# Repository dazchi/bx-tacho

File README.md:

# BX Tacho

**English** | [繁體中文](README.zh-TW.md)

An open, DIY launch RPM meter for **Beyblade X** launchers. It clips onto the
back of the launcher, reads the launcher's spinning black/white pattern with an
IR sensor, and shows the launch RPM on a small OLED.

**Web app: [dazchi.github.io/bx-tacho](https://dazchi.github.io/bx-tacho/)**
(Chrome or Edge on a computer, Chrome on Android)

## What it does

- **Measures launch RPM** optically, up to about 20,000 RPM, and shows the
  result and the peak on the display.
- **Senses when a Bey is loaded** and when it's released, so each shot is
  recorded automatically: no buttons to press.
- **Keeps a shot history:** the last 50 shots, the total count, the best shot
  and the latest launch curve.
- **Bluetooth:** uses the Bey Battle Pass protocol, so Battle Pass apps can
  read your shots.
- **Runs on a 1S LiPo** with USB-C charging, a power switch, battery monitoring,
  and sleep when idle.
- **Left-handed mode:** the display can be turned 180°.

## Web app

The [web app](https://dazchi.github.io/bx-tacho/) runs in the browser, with
nothing to install:

- **Bluetooth:** live shot data, battery, the launch curve and your history.
- **Firmware updates** over USB or Bluetooth, with one click for the latest
  release.
- **A console** over USB or Bluetooth, for settings, calibration and
  diagnostics.

It's available in English, 繁體中文, 简体中文 and 日本語. Details:
[web/README.md](web/README.md).

## Hardware

An ESP32-C3 (ESP32-C3-WROOM-02) with two ITR8307 reflective IR sensors:
- one reads the RPM, through an LMV331 comparator;
- one detects a loaded Bey.

The rest of the board:
- a 0.96″ SSD1315 OLED;
- a TP4054 charger, with load sharing so it runs while charging;
- USB-C for power and data.

- [hardware/](hardware/): KiCad 10 project (schematic, PCB, footprints, 3D
  models). Gerbers and the BOM for JLCPCB assembly are in the
  [hardware v1.0 release](https://github.com/dazchi/bx-tacho/releases/tag/hw-v1.0).
- [mechanical/](mechanical/): STL files for the 3D-printed case:
  `case_top`, `case_bottom` and the launcher `clip`.

## Firmware

ESP-IDF v6.1 firmware in [firmware/](firmware/).

**Installing it:** use the web app's update button, or download the firmware
from [Releases](https://github.com/dazchi/bx-tacho/releases). Your settings
and shot history are kept.

**Building it yourself:**

```bash
cd firmware
idf.py build
idf.py -p COMx flash monitor
```

Build options, the console commands, calibration and the Bluetooth protocols
are covered in [firmware/README.md](firmware/README.md).

## License

[GPL-3.0-or-later](LICENSE). Copyright © 2026 Darren Chi
([github.com/dazchi](https://github.com/dazchi)). See [NOTICE](NOTICE) for
the exception covering the optional firmware extension.

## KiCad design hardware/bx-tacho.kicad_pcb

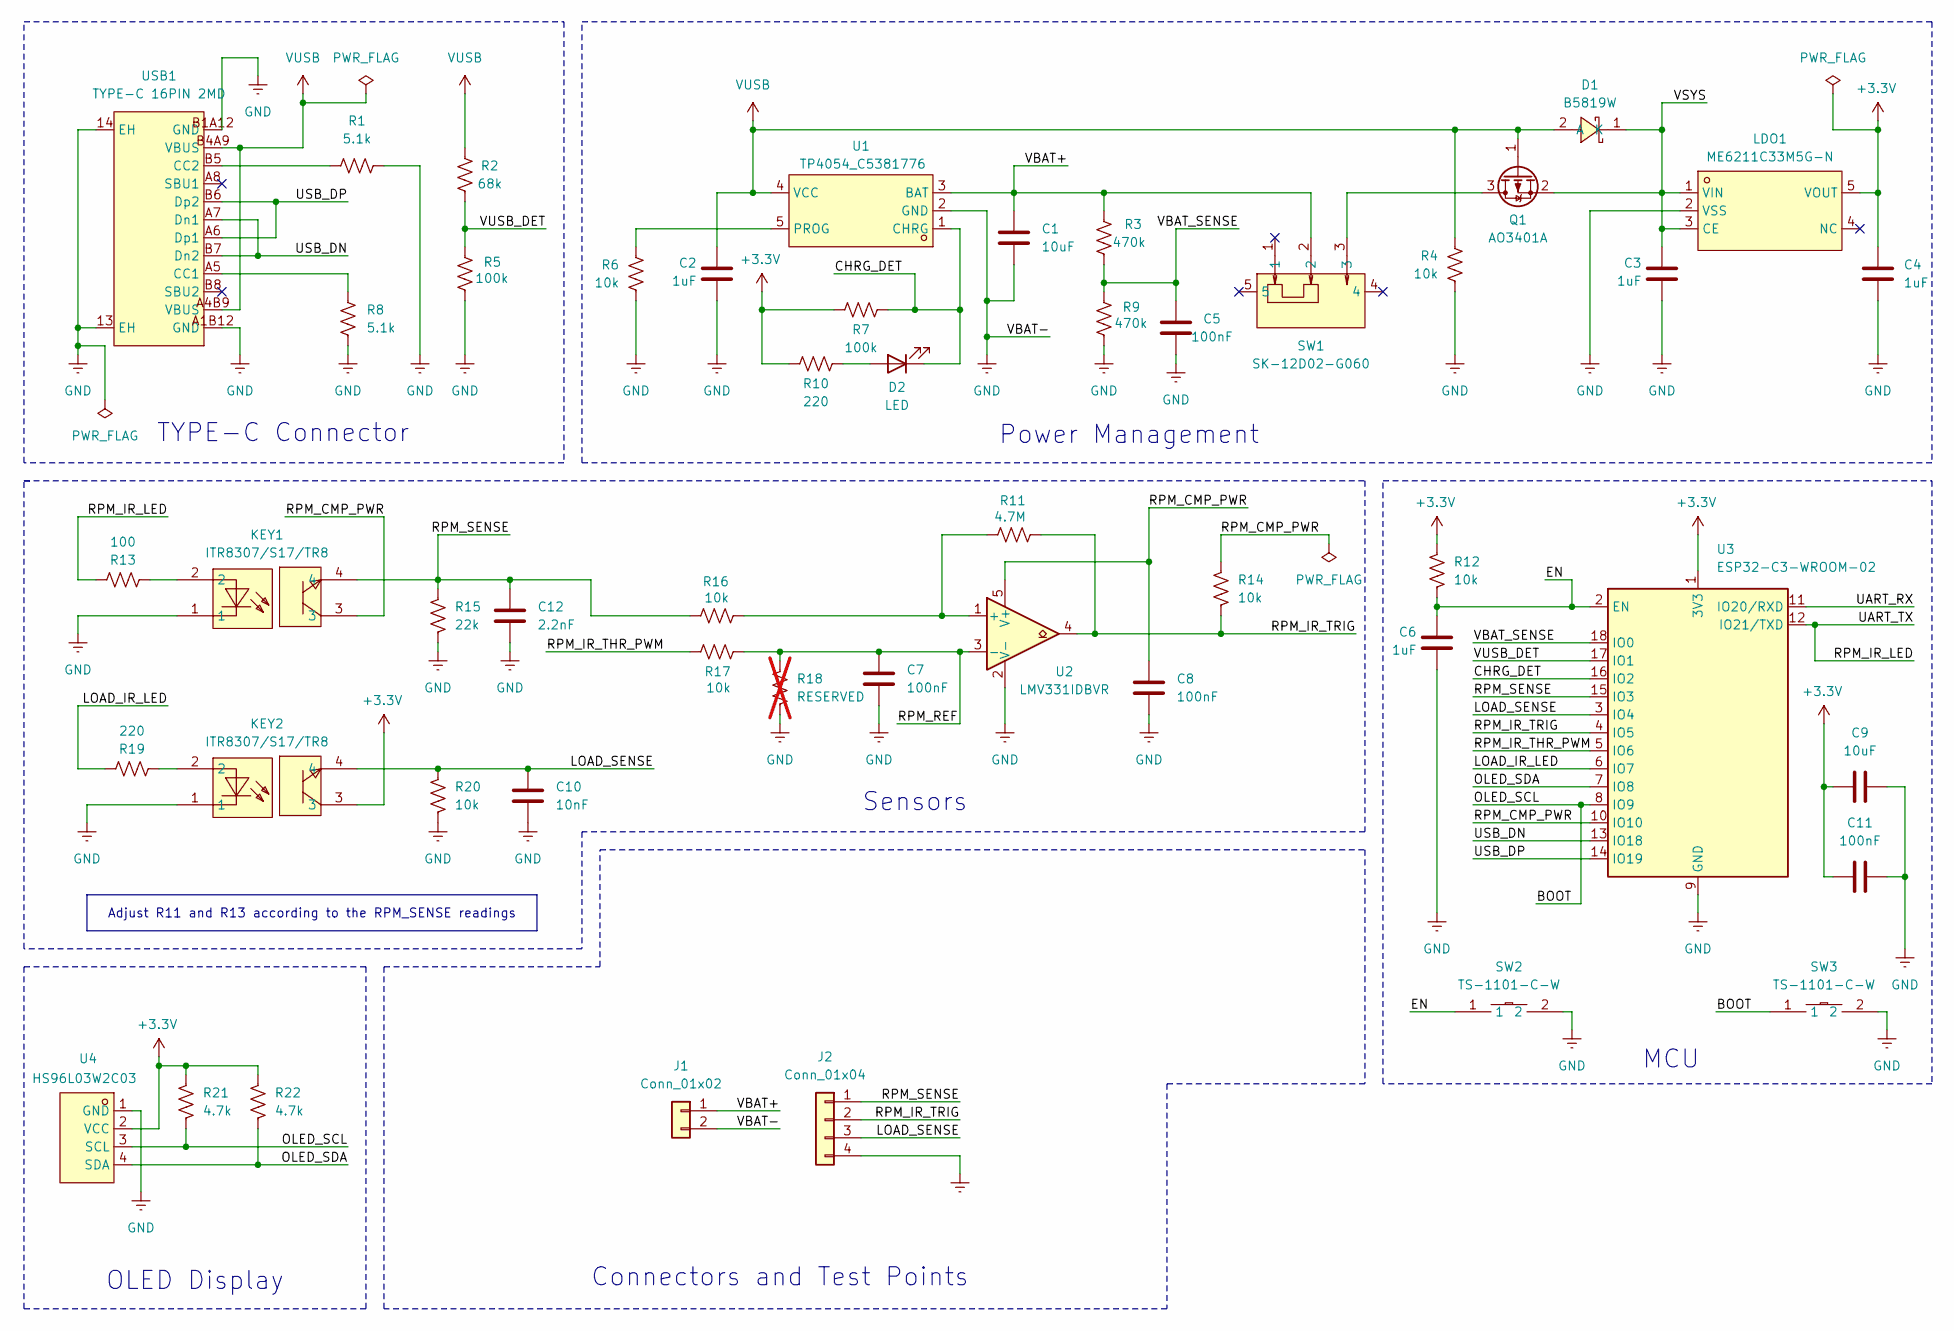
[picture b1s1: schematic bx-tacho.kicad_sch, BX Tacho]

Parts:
C1, C9: 10uF; C_0805_2012Metric; LCSC C15850
C2, C3, C4, C6: 1uF; C_0603_1608Metric; LCSC C15849
C5, C7, C8, C11: 100nF; C_0603_1608Metric; LCSC C14663
C10: 10nF; C_0603_1608Metric; LCSC C57112
C12: 2.2nF; C_0603_1608Metric; LCSC C1604
D1: B5819W; SOD-123F_L2.7-W1.6-LS3.8-RD-1; MPN B5819W SL; LCSC Part C8598
D2: LED; LED_0603_1608Metric_Pad1.05x0.95mm_HandSolder; LCSC C2286
J1: Conn_01x02; BatteryPads_1x02_SMD_2x3mm_P4mm
J2: Conn_01x04; PinHeader_1x04_P2.54mm_Vertical
KEY1, KEY2: ITR8307/S17/TR8; OPTO-SMD_ITR8307-S17-TR8-B-BL; MPN ITR8307/S17/TR8(B); LCSC Part C81632
LDO1: ME6211C33M5G-N; SOT-23-5_L3.0-W1.7-P0.95-LS2.8-BL; MPN ME6211C33M5G-N; LCSC Part C82942
Q1: AO3401A; SOT-23; LCSC C15127
R1, R8: 5.1k; R_0603_1608Metric; LCSC C23186
R2: 68k; R_0603_1608Metric; LCSC C23231
R3, R9: 470k; R_0603_1608Metric; LCSC C23178
R4, R6, R12, R14, R16, R17, R20: 10k; R_0603_1608Metric; LCSC C25804
R5, R7: 100k; R_0603_1608Metric; LCSC C25803
R10, R19: 220; R_0603_1608Metric; LCSC C22962
R11: 4.7M; R_0603_1608Metric; LCSC C2930153
R13: 100; R_0603_1608Metric; LCSC C22775
R15: 22k; R_0603_1608Metric; LCSC C31850
R18: RESERVED; R_0603_1608Metric; not fitted
R21, R22: 4.7k; R_0603_1608Metric; LCSC C23162
SW1: SK-12D02-G060; SW-TH_SK-12D02-G060; MPN SK-12D02-G060; LCSC Part C2848884
SW2, SW3: TS-1101-C-W; SW-SMD_L6.0-W3.3-LS8.0_TS-1101-C-W; MPN TS-1101-C-W; LCSC Part C318938
U1: TP4054_C5381776; SOT-23-5_L2.9-W1.6-P0.95-LS2.8-BR; MPN TP4054; LCSC Part C5381776
U2: LMV331IDBVR; SOT-23-5_L3.0-W1.7-P0.95-LS2.8-BR; LCSC Part C34731
U3: ESP32-C3-WROOM-02; LCSC C2934560
U4: HS96L03W2C03; OLED-TH_L27.8-W27.2-P2.54_C9900033791; MPN HS96L03W2C03; LCSC Part C5248080
USB1: TYPE-C 16PIN 2MD; USB-C-SMD_TYPE-C-16PIN-2MD-073; MPN TYPE-C 16PIN 2MD(073); LCSC Part C2765186

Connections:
+3.3V: C4.1, C9.2, C11.2, KEY2.3, LDO1.5 (VOUT), R7.1, R10.1, R12.1, R21.1, R22.1, U3.1 (3V3), U4.2 (VCC)
/BOOT: R21.2, SW3.1, U3.8 (IO9), U4.3 (SCL)
/CHRG_DET: D2.1 (K), R7.2, U1.1 (CHRG), U3.16 (IO2)
/EN: C6.1, R12.2, SW2.1, U3.2 (EN)
/LOAD_IR_LED: R19.2, U3.6 (IO7)
/LOAD_SENSE: C10.1, J2.3, KEY2.4, R20.1, U3.3 (IO4)
/OLED_SDA: R22.2, U3.7 (IO8), U4.4 (SDA)
/RPM_CMP_PWR: C8.1, KEY1.3, R14.1, U2.5 (V+), U3.10 (IO10)
/RPM_IR_LED: R13.2, U3.12 (IO21/TXD)
/RPM_IR_THR_PWM: R17.2, U3.5 (IO6)
/RPM_IR_TRIG: J2.2, R11.1, R14.2, U2.4, U3.4 (IO5)
/RPM_REF: C7.1, R17.1, R18.1, U2.3 (-)
/RPM_SENSE: C12.1, J2.1, KEY1.4, R15.1, R16.2, U3.15 (IO3)
/UART_RX: U3.11 (IO20/RXD)
/USB_DN: U3.13 (IO18), USB1.A7 (Dn1), USB1.B7 (Dn2)
/USB_DP: U3.14 (IO19), USB1.A6 (Dp1), USB1.B6 (Dp2)
/VBAT+: C1.1, J1.1, R3.2, SW1.2, U1.3 (BAT)
/VBAT_SENSE: C5.1, R3.1, R9.2, U3.18 (IO0)
/VSYS: C3.1, D1.1 (K), LDO1.1 (VIN), LDO1.3 (CE), Q1.2 (S)
/VUSB_DET: R2.1, R5.2, U3.17 (IO1)
GND: C1.2, C2.2, C3.2, C4.2, C5.2, C6.2, C7.2, C8.2, C9.1, C10.2, C11.1, C12.2, J1.2, J2.4, KEY1.1, KEY2.1, LDO1.2 (VSS), R1.2, R4.2, R5.1, R6.2, R8.2, R9.1, R15.2, R18.2, R20.2, SW2.2, SW3.2, U1.2 (GND), U2.2 (V-), U3.9 (GND), U3.19 (GND), U4.1 (GND), USB1.13 (EH), USB1.14 (EH), USB1.A1B12 (GND), USB1.B1A12 (GND)
unnamed: D2.2 (A), R10.2
unnamed: KEY1.2, R13.1
unnamed: KEY2.2, R19.1
unnamed: Q1.3 (D), SW1.3
unnamed: R6.1, U1.5 (PROG)
unnamed: R11.2, R16.1, U2.1 (+)
unnamed: R8.1, USB1.A5 (CC1)
unnamed: R1.1, USB1.B5 (CC2)
VUSB: C2.1, D1.2 (A), Q1.1 (G), R2.2, R4.1, U1.4 (VCC), USB1.A4B9 (VBUS), USB1.B4A9 (VBUS)

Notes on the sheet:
MCU
Sensors
TYPE-C Connector
Connectors and Test Points
Power Management
OLED Display
Adjust R11 and R13 according to the RPM_SENSE readings

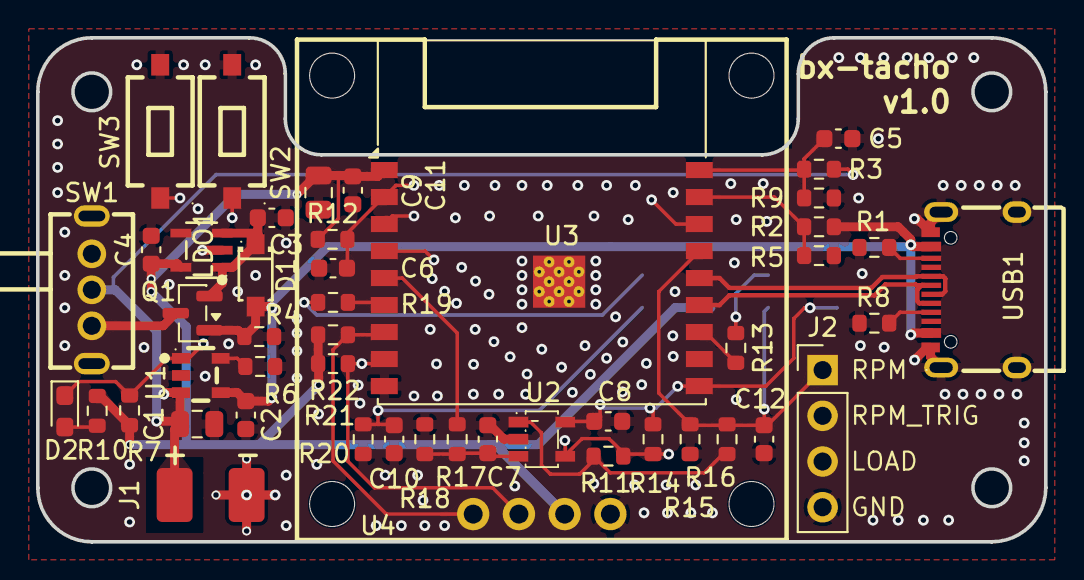
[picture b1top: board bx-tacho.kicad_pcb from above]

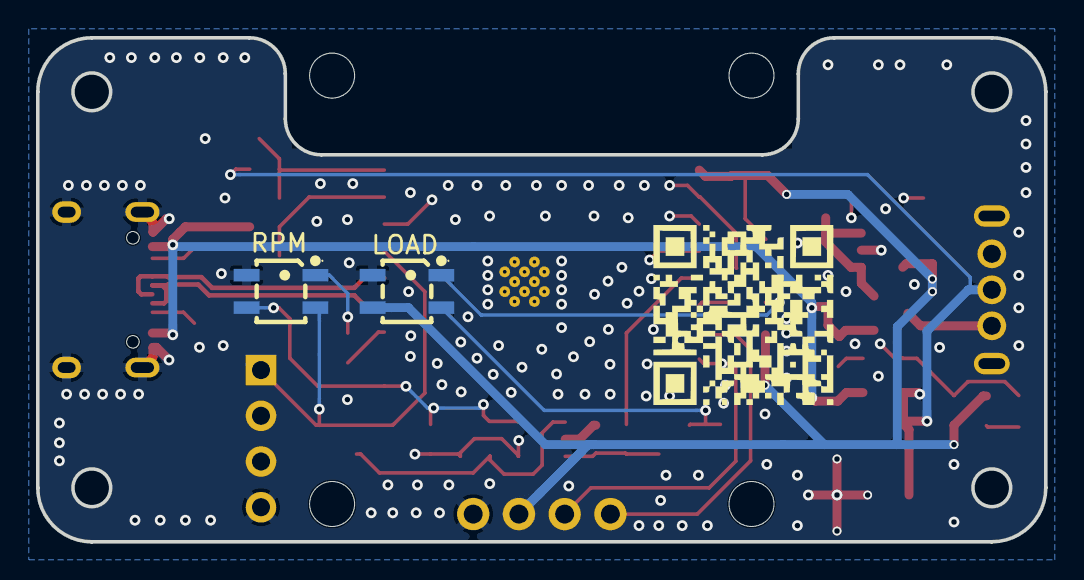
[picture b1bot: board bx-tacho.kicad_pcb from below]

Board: 4 copper layers, 56.0 x 28.0 mm, 50 parts (2 on the bottom side), 29 nets.

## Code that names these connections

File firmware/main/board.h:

// SPDX-License-Identifier: GPL-3.0-or-later
// Copyright (C) 2026 Darren Chi
// Pin map for the BX Tacho v0.2 board (ESP32-C3-WROOM-02).
// See HANDOVER.md section 3.9.
#pragma once

#include "driver/gpio.h"
#include "hal/adc_types.h"

// Power and charger monitoring
#define PIN_VBAT_SENSE      GPIO_NUM_0   // ADC1_CH0, VBAT / 2 (R3/R9 470k/470k)
#define PIN_VUSB_DET        GPIO_NUM_1   // HIGH = USB present, deep-sleep wake source
#define PIN_CHRG_DET        GPIO_NUM_2   // LOW = charging (TP4054 CHRG, R7 pull-up), strap pin

// RPM channel (KEY1 + LMV331)
#define PIN_RPM_SENSE       GPIO_NUM_3   // ADC1_CH3, phototransistor emitter, valid only while powered
#define PIN_RPM_IR_TRIG     GPIO_NUM_5   // comparator output, rising-edge interrupt
#define PIN_RPM_THR_PWM     GPIO_NUM_6   // 100 kHz LEDC, RC-filtered to RPM_REF
#define PIN_RPM_CMP_PWR     GPIO_NUM_10  // supplies comparator, pull-up and KEY1 collector
#define PIN_RPM_IR_LED      GPIO_NUM_21  // KEY1 LED (U0TXD, flickers with the ROM boot log)

// Load-detect channel (KEY2)
#define PIN_LOAD_SENSE      GPIO_NUM_4   // ADC1_CH4
#define PIN_LOAD_IR_LED     GPIO_NUM_7   // KEY2 LED

// OLED (SSD1315, I2C). IO8/IO9 are strap pins held high by R21/R22.
#define PIN_OLED_SDA        GPIO_NUM_8
#define PIN_OLED_SCL        GPIO_NUM_9   // shared with the BOOT button (SW3)

#define ADC_CH_VBAT         ADC_CHANNEL_0
#define ADC_CH_RPM_SENSE    ADC_CHANNEL_3
#define ADC_CH_LOAD_SENSE   ADC_CHANNEL_4

// Supply the threshold PWM is referenced to
#define BOARD_VDD_MV        3300
